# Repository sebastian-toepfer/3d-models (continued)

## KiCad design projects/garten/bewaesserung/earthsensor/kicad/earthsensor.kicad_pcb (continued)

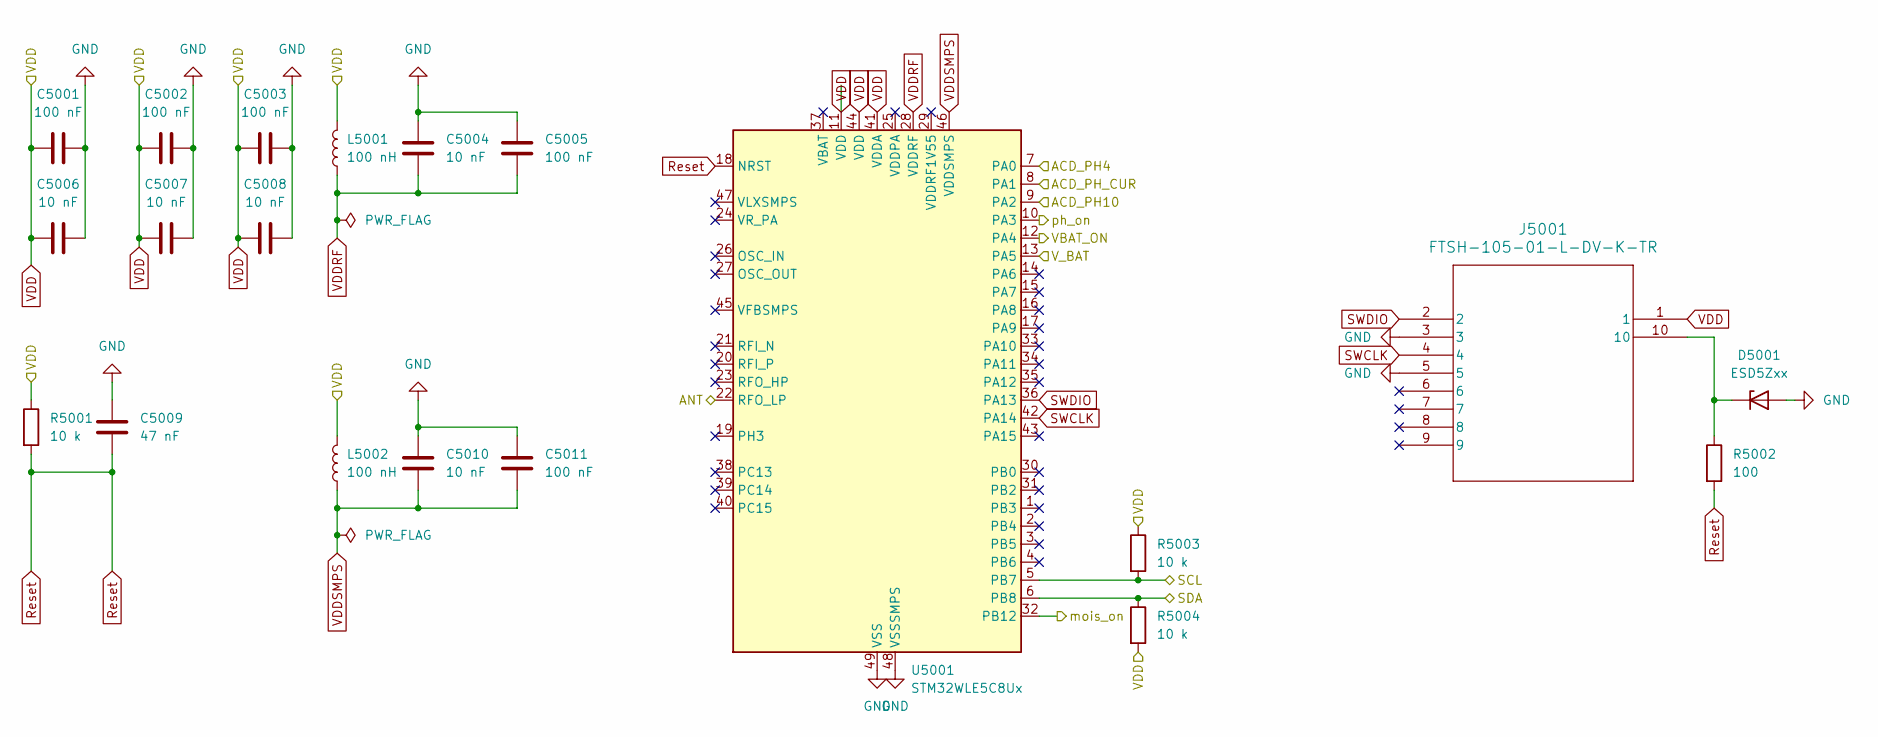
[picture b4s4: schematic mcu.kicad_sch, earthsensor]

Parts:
C5001, C5002, C5003, C5005, C5011: 100 nF; C_0805_2012Metric; MPN GCM21BR72A104KA37L
C5004, C5006, C5007, C5008, C5010: 10 nF; C_0805_2012Metric; MPN GRM2195C1H103FA01D
C5009: 47 nF; C_0805_2012Metric; MPN GCM21BR72A473KA37L
D5001: ESD5Zxx; D_SOD-523; MPN PESD5Z3.3-QX
J5001: FTSH-105-01-L-DV-K-TR; CON10_2X5_DUK_FTSH_SAI; MPN FTSH-105-01-L-DV-K-TR
L5001, L5002: 100 nH; L_0402_1005Metric; MPN LQW15ANR10J00D
R5001, R5003, R5004: 10 k; R_0402_1005Metric; MPN RN73H1ETTP1002B25
R5002: 100; R_0402_1005Metric; MPN RN73H1ETTP1000B25
U5001: STM32WLE5C8Ux; QFN-48-1EP_7x7mm_P0.5mm_EP5.6x5.6mm; MPN STM32WLE5C8U6

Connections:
/I2C.SCL: R5003.2, U5001.5 (PB7); also elsewhere on the board
/I2C.SDA: R5004.1, U5001.6 (PB8); also elsewhere on the board
/antenna/ANT: U5001.22 (RFO_LP); also elsewhere on the board
/mcu/ACD_PH4: U5001.7 (PA0); also elsewhere on the board
/mcu/ACD_PH10: U5001.9 (PA2); also elsewhere on the board
/mcu/ACD_PH_CUR: U5001.8 (PA1); also elsewhere on the board
/mcu/VBAT_ON: U5001.12 (PA4); also elsewhere on the board
/mcu/V_BAT: U5001.13 (PA5); also elsewhere on the board
/mcu/mois_on: U5001.32 (PB12); also elsewhere on the board
/mcu/ph_on: U5001.10 (PA3); also elsewhere on the board
GND: C5001.2, C5002.2, C5003.1, C5004.1, C5005.1, C5006.2, C5007.2, C5008.1, C5009.1, C5010.1, C5011.1, D5001.2 (A), J5001.3, J5001.5, U5001.48 (VSSSMPS), U5001.49 (VSS); also elsewhere on the board
unnamed: D5001.1 (K), J5001.10, R5002.1
Reset: C5009.2, R5001.2, R5002.2, U5001.18 (NRST)
SWCLK: J5001.4, U5001.42 (PA14)
SWDIO: J5001.2, U5001.36 (PA13)
VDD: C5001.1, C5002.1, C5003.2, C5006.1, C5007.1, C5008.2, J5001.1, L5001.2, L5002.2, R5001.1, R5003.1, R5004.2, U5001.11 (VDD), U5001.41 (VDDA), U5001.44 (VDD); also elsewhere on the board
VDDRF: C5004.2, C5005.2, L5001.1, U5001.28 (VDDRF)
VDDSMPS: C5010.2, C5011.2, L5002.1, U5001.46 (VDDSMPS)

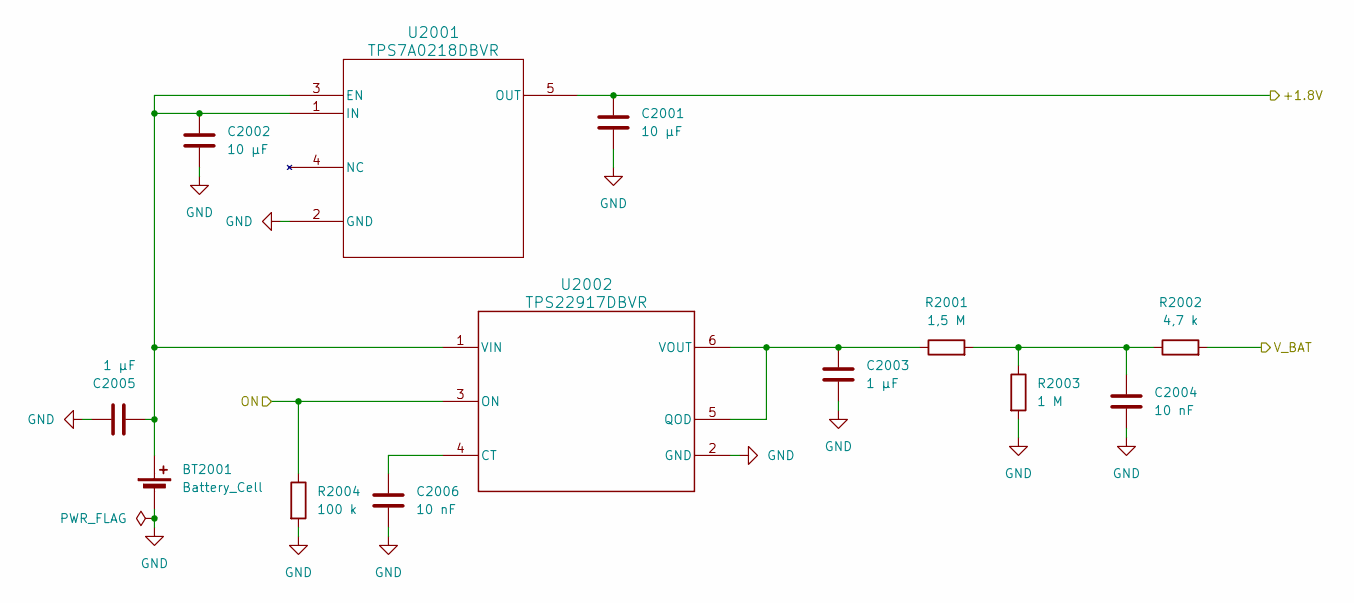
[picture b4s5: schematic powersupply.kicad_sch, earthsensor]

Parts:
BT2001: Battery_Cell; BAT_1016; MPN 1016
C2001, C2002: 10 µF; C_0805_2012Metric; MPN GRM21BR71A106KE51L
C2003, C2005: 1 µF; C_0805_2012Metric; MPN GCJ21BR71H105KA01L
C2004, C2006: 10 nF; C_0805_2012Metric; MPN GRM2195C1H103FA01D
R2001: 1,5 M; R_0402_1005Metric; MPN RK73H1ETTP1504F
R2002: 4,7 k; R_0402_1005Metric; MPN RN73R1ETTP4701B25
R2003: 1 M; R_0402_1005Metric; MPN RK73H1ETTP1004F
R2004: 100 k; R_0402_1005Metric; MPN RN73H1ETTP1003B25
U2001: TPS7A0218DBVR; SOT23_DBV_TEX-L; MPN TPS7A0218DBVR
U2002: TPS22917DBVR; DBV0006_N; MPN TPS22917DBVR

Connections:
/mcu/VBAT_ON: R2004.1, U2002.3 (ON); also elsewhere on the board
/mcu/V_BAT: R2002.2; also elsewhere on the board
GND: BT2001.2 (-), C2001.1, C2002.1, C2003.2, C2004.2, C2005.1, C2006.2, R2003.2, R2004.2, U2001.2 (GND), U2002.2 (GND); also elsewhere on the board
unnamed: BT2001.1 (+), C2002.2, C2005.2, U2001.1 (IN), U2001.3 (EN), U2002.1 (VIN)
unnamed: C2004.1, R2001.2, R2002.1, R2003.1
unnamed: C2006.1, U2002.4 (CT)
unnamed: C2003.1, R2001.1, U2002.5 (QOD), U2002.6 (VOUT)
VDD: C2001.2, U2001.5 (OUT); also elsewhere on the board

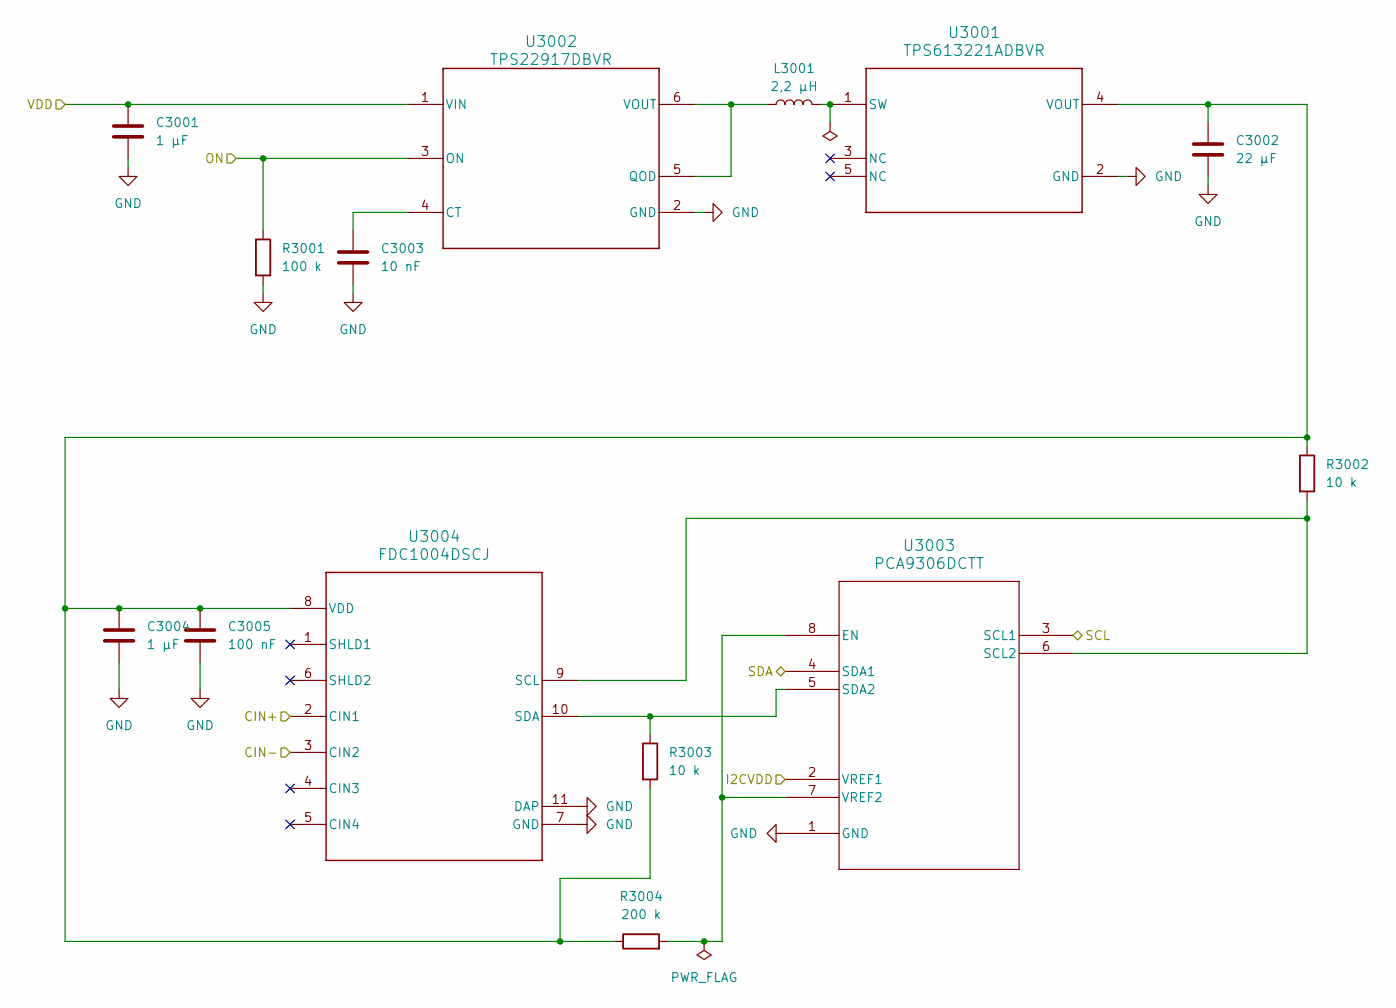
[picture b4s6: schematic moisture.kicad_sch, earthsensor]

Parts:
C3001, C3004: 1 µF; C_0805_2012Metric; MPN GCJ21BR71H105KA01L
C3002: 22 µF; C_1206_3216Metric; MPN GRM31CR71A226KE15K
C3003: 10 nF; C_0805_2012Metric; MPN GRM2195C1H103FA01D
C3005: 100 nF; C_0805_2012Metric; MPN GCM21BR72A104KA37L
L3001: 2,2 µH; L_0603_1608Metric; MPN LQM18PN2R2MGHD
R3001: 100 k; R_0402_1005Metric; MPN RN73H1ETTP1003B25
R3002, R3003: 10 k; R_0402_1005Metric; MPN RN73H1ETTP1002B25
R3004: 200 k; R_0402_1005Metric; MPN RN73H1ETTP2003B25
U3001: TPS613221ADBVR; DBV0005A_N; MPN TPS613221ADBVR
U3002: TPS22917DBVR; DBV0006_N; MPN TPS22917DBVR
U3003: PCA9306DCTT; DCT8; MPN PCA9306DCTT
U3004: FDC1004DSCJ; DSC0010B; MPN FDC1004DSCJ

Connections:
/I2C.SCL: U3003.4 (SDA1); also elsewhere on the board
/I2C.SDA: U3003.3 (SCL1); also elsewhere on the board
/mcu/mois_on: R3001.1, U3002.3 (ON); also elsewhere on the board
GND: C3001.2, C3002.2, C3003.2, C3004.2, C3005.2, R3001.2, U3001.2 (GND), U3002.2 (GND), U3003.1 (GND), U3004.7 (GND), U3004.11 (DAP); also elsewhere on the board
unnamed: L3001.2, U3001.1 (SW)
unnamed: C3002.1, C3004.1, C3005.1, R3002.1, R3003.2, R3004.1, U3001.4 (VOUT), U3004.8 (VDD)
unnamed: C3003.1, U3002.4 (CT)
unnamed: L3001.1, U3002.5 (QOD), U3002.6 (VOUT)
unnamed: R3004.2, U3003.7 (VREF2), U3003.8 (EN)
unnamed: R3002.2, U3003.6 (SCL2), U3004.9 (SCL)
unnamed: R3003.1, U3003.5 (SDA2), U3004.10 (SDA)
V2A_right: U3004.3 (CIN2); also elsewhere on the board
V2A_top: U3004.2 (CIN1); also elsewhere on the board
VDD: C3001.1, U3002.1 (VIN), U3003.2 (VREF1); also elsewhere on the board

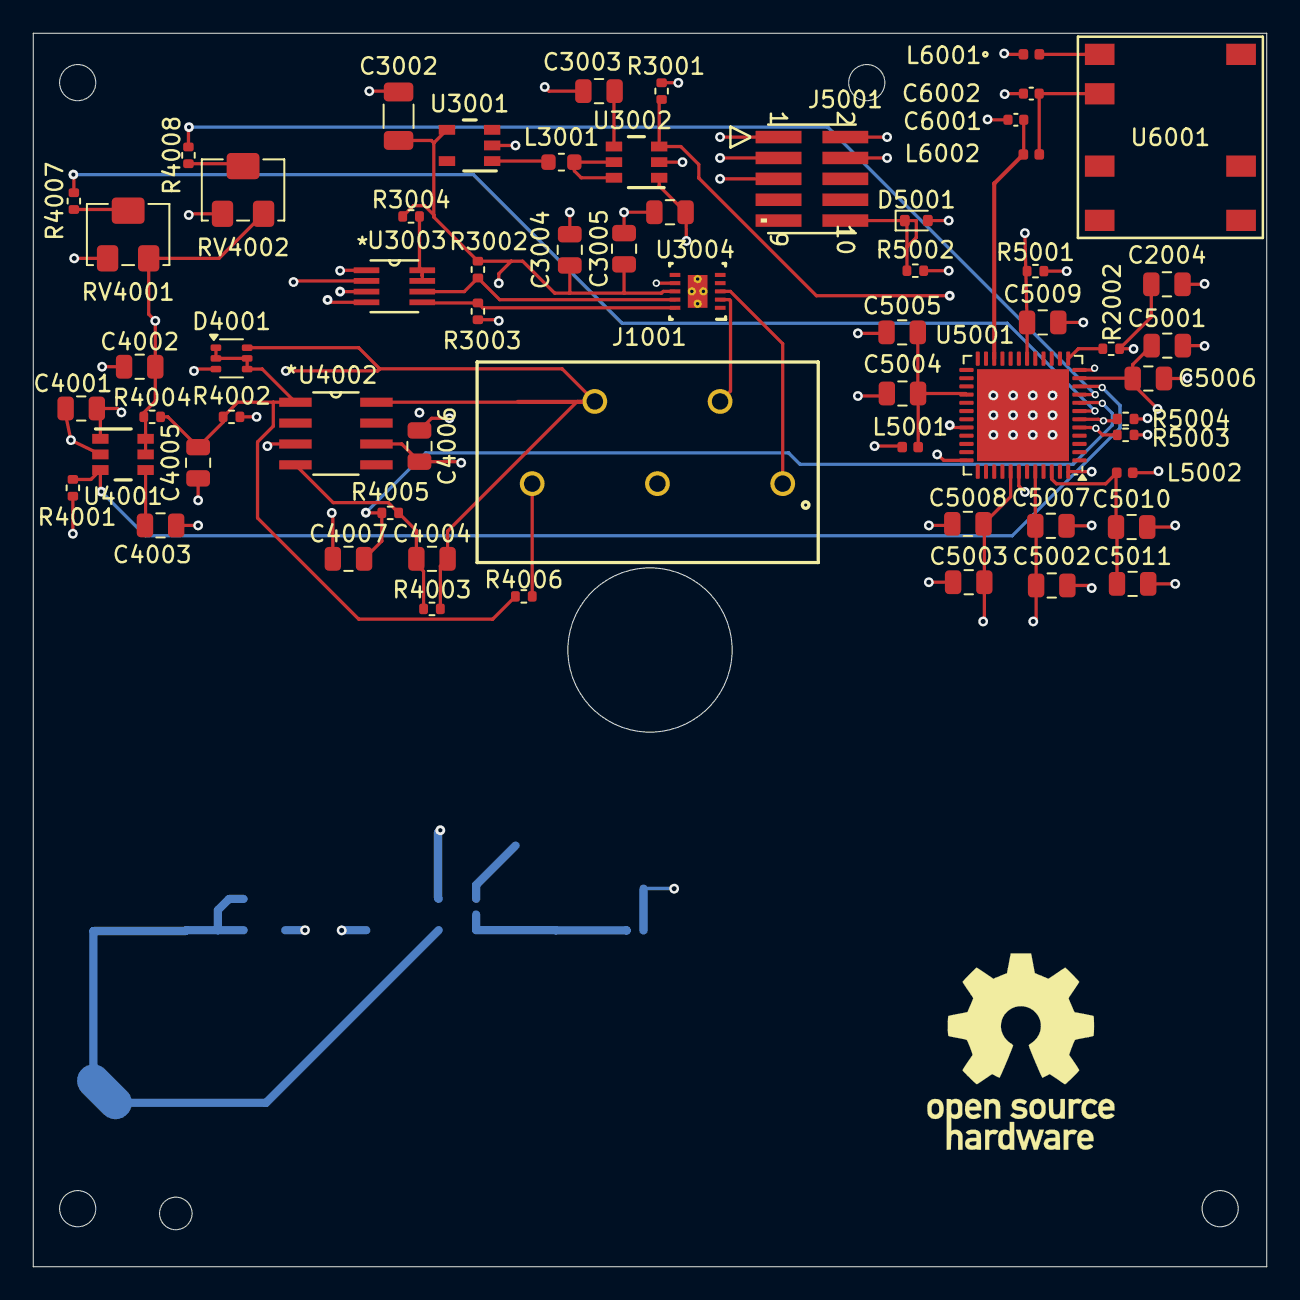
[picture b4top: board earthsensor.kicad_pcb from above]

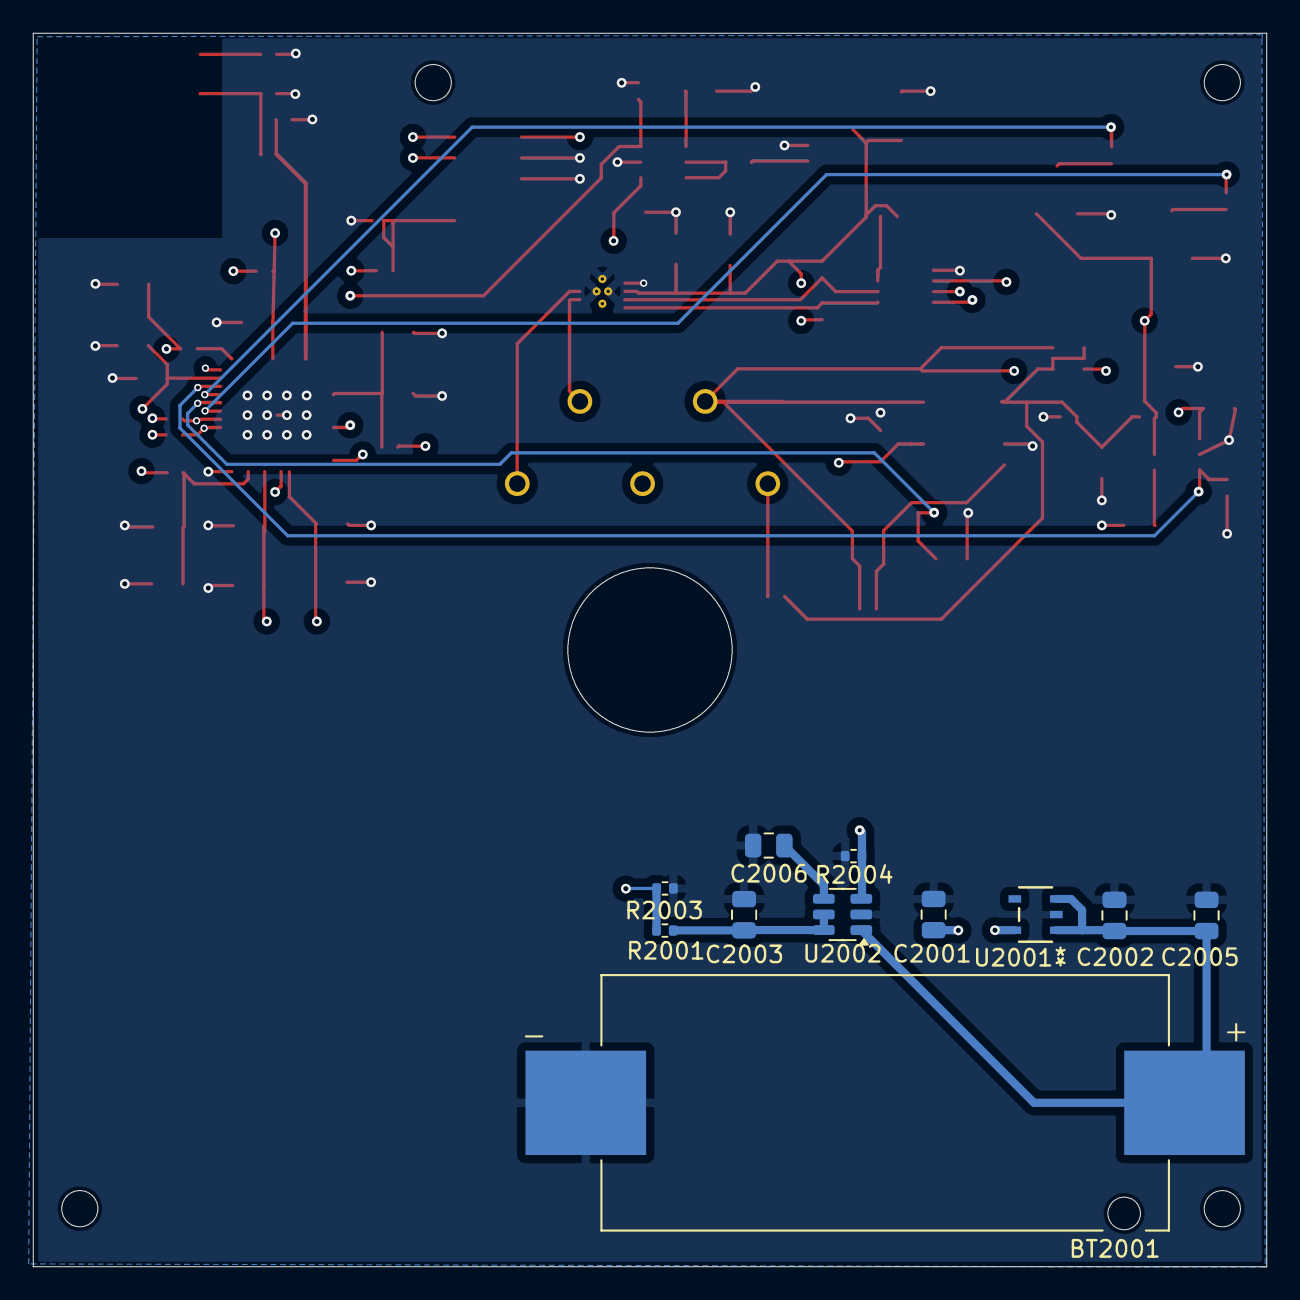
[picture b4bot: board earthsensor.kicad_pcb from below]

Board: 4 copper layers, 75.0 x 75.0 mm, 73 parts (11 on the bottom side), 41 nets.

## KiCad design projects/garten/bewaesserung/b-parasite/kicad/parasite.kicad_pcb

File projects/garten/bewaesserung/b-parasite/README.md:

This project is completly based on:

https://github.com/rbaron/b-parasite

⚠️  It has a difference License than the rest of my projects!

# License
The hardware and associated design files are released under the [Creative Commons CC BY-SA 4.0 license](https://creativecommons.org/licenses/by-sa/4.0/).
The code is released under the [MIT license](https://opensource.org/licenses/MIT).

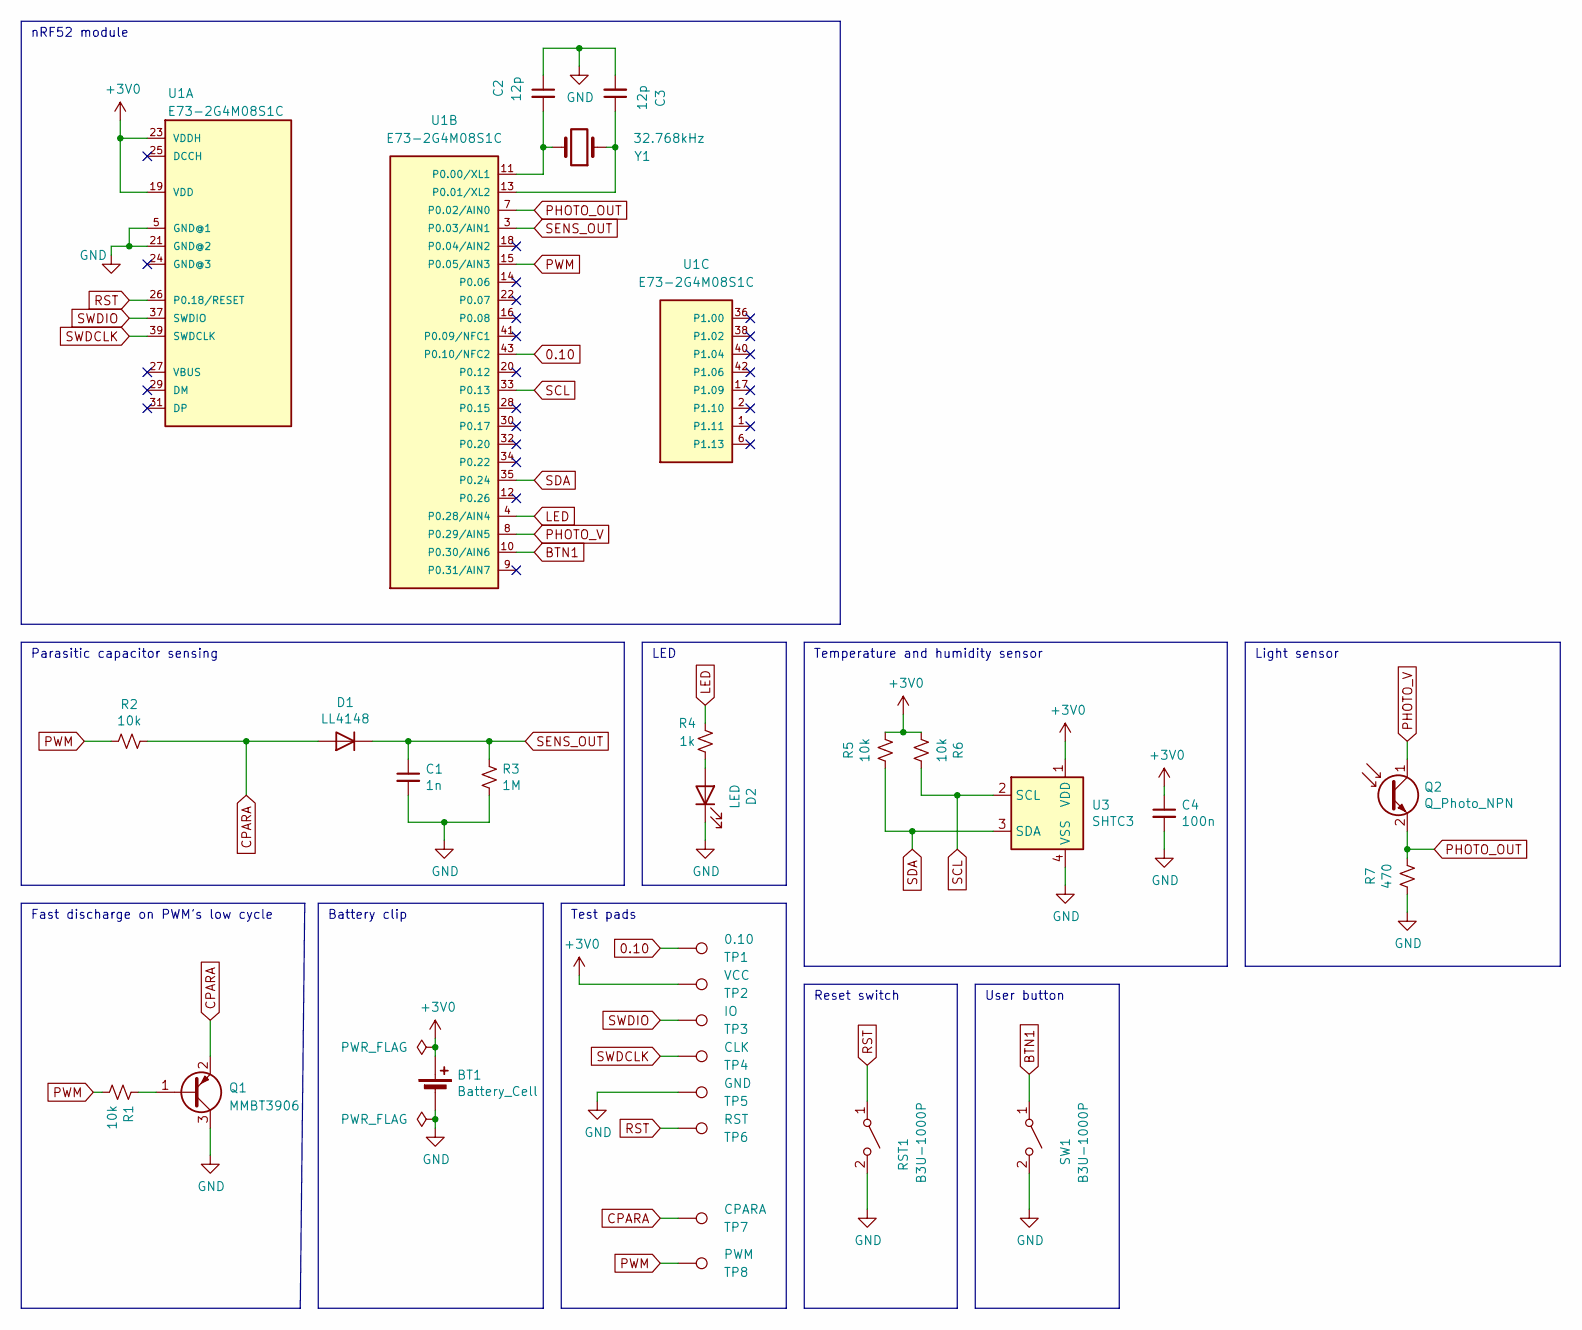
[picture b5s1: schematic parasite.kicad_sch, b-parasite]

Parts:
BT1: Battery_Cell; BatteryHolder_Keystone_3002_1x2032; MPN 3002TR
C1: 1n; C_0402_1005Metric; LCSC C1523
C2, C3: 12p; C_0402_1005Metric; MPN GRM1555C1H120GA01D; LCSC C1547
C4: 100n; C_0402_1005Metric; MPN GRM155R71A104KA01D; LCSC C1525
D1: LL4148; D_MiniMELF; MPN LL4148-GS18; LCSC C3011166
D2: LED; LED_0603_1608Metric; LCSC C2286
Q1: MMBT3906; SOT-23; MPN PZT3906; LCSC C2910191
Q2: Q_Photo_NPN; TR8; MPN ALS-PT19-315C/L177/TR8; LCSC C146233
R1, R2, R5, R6: 10k; R_0402_1005Metric; MPN CRGCQ0402F10K; LCSC C25744
R3: 1M; R_0402_1005Metric; MPN CRGCQ0402F1M0; LCSC C26083
R4: 1k; R_0402_1005Metric; MPN CRGCQ0402F1K0; LCSC C11702
R7: 470; R_0402_1005Metric; MPN RLP73N1ER47FTDF; LCSC C25117
RST1: B3U-1000P; SW_SPST_B3U-1000P; MPN B3U-1000P; LCSC C231329
SW1: B3U-1000P; SW_SPST_B3U-1000P; MPN B3U-1000P; LCSC C231329
TP1: 0.10; TestPoint_Pad_D1.0mm
TP2: VCC; TestPoint_Pad_D1.0mm
TP3: IO; TestPoint_Pad_D1.0mm
TP4: CLK; TestPoint_Pad_D1.0mm
TP5: GND; TestPoint_Pad_D1.0mm
TP6: RST; TestPoint_Pad_D1.0mm
TP7: CPARA; TestPoint_Pad_D1.0mm
TP8: PWM; TestPoint_Pad_D1.0mm
U1: E73-2G4M08S1C; MPN E73-2G4M08S1C
U3: SHTC3; Sensirion_DFN-4-1EP_2x2mm_P1mm_EP0.7x1.6mm; LCSC C194656
Y1: 32.768kHz; Crystal_SMD_3215-2Pin_3.2x1.5mm; MPN FC-135 32.7680KA-AC0; LCSC C32346

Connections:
0.10: TP1.1, U1.43 (P0.10/NFC2)
+3V0: BT1.1 (+), C4.1, R5.2, R6.1, TP2.1, U1.19 (VDD), U1.23 (VDDH), U3.1 (VDD)
BTN1: SW1.1 (A), U1.10 (P0.30/AIN6)
CPARA: D1.2 (A), Q1.2 (E), R2.2, TP7.1
GND: BT1.2 (-), C1.2, C2.1, C3.2, C4.2, D2.1 (K), Q1.3 (C), R3.2, R7.1, RST1.2 (B), SW1.2 (B), TP5.1, U1.5 (GND@1), U1.21 (GND@2), U3.4 (VSS)
LED: R4.2, U1.4 (P0.28/AIN4)
unnamed: D2.2 (A), R4.1
unnamed: Q1.1 (B), R1.1
unnamed: C2.2, U1.11 (P0.00/XL1), Y1.2
unnamed: C3.1, U1.13 (P0.01/XL2), Y1.1
PHOTO_OUT: Q2.2 (E), R7.2, U1.7 (P0.02/AIN0)
PHOTO_V: Q2.1 (C), U1.8 (P0.29/AIN5)
PWM: R1.2, R2.1, TP8.1, U1.15 (P0.05/AIN3)
RST: RST1.1 (A), TP6.1, U1.26 (P0.18/RESET)
SCL: R6.2, U1.33 (P0.13), U3.2 (SCL)
SDA: R5.1, U1.35 (P0.24), U3.3 (SDA)
SENS_OUT: C1.1, D1.1 (K), R3.1, U1.3 (P0.03/AIN1)
SWDCLK: TP4.1, U1.39 (SWDCLK)
SWDIO: TP3.1, U1.37 (SWDIO)

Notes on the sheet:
Fast discharge on PWM’s low cycle
Temperature and humidity sensor
LED
nRF52 module
Parasitic capacitor sensing
Test pads
Light sensor
Reset switch
User button
Battery clip

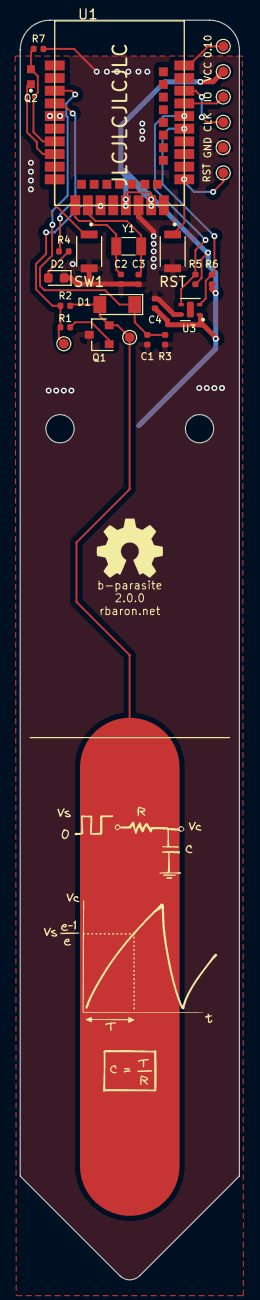
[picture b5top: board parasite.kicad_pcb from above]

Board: 2 copper layers, 22.0 x 126.4 mm, 29 parts (1 on the bottom side), 19 nets.

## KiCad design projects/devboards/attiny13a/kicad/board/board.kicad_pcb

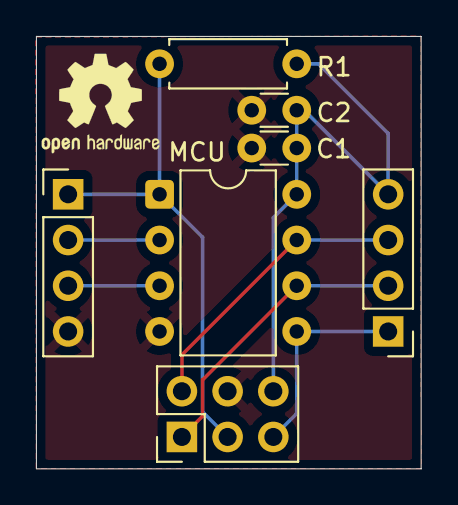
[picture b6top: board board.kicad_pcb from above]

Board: 2 copper layers, 21.4 x 24.0 mm, 7 parts (0 on the bottom side), 8 nets.

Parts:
C1: 10 nF; C_Disc_D3.0mm_W1.6mm_P2.50mm
C2: 100 nF; C_Disc_D3.0mm_W1.6mm_P2.50mm
J2: USBasp; PinHeader_2x03_P2.54mm_Vertical
J3: PinLeiste_Links; PinHeader_1x04_P2.54mm_Vertical
J4: PinLeiste_Rechts; PinHeader_1x04_P2.54mm_Vertical
MCU: Federkontakt; DIP-8_W7.62mm
R1: 10k; R_Axial_DIN0207_L6.3mm_D2.5mm_P7.62mm_Horizontal

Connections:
+5V: C1.1, C2.1, J2.6, J4.4, MCU.8, R1.1
COPI: J2.5, J4.1, MCU.5
GND: C1.2, C2.2, J2.4, J3.4, MCU.4
PB3: J3.2, MCU.2
PB4: J3.3, MCU.3
PICO: J2.1, J4.2, MCU.6
RESET: J2.3, J3.1, MCU.1, R1.2
SCK: J2.2, J4.3, MCU.7

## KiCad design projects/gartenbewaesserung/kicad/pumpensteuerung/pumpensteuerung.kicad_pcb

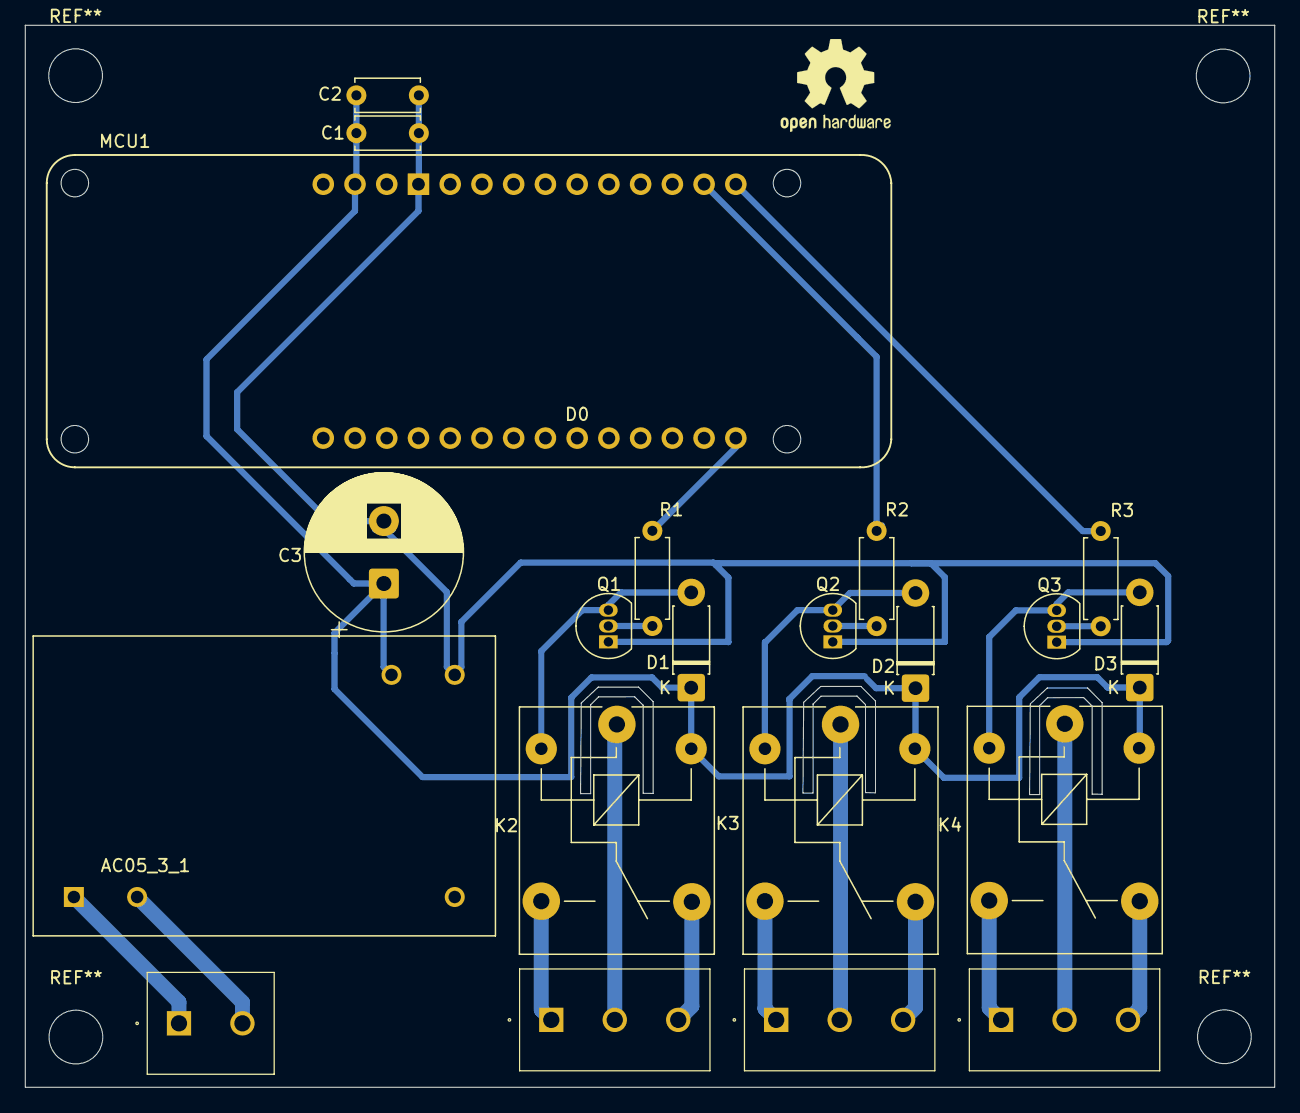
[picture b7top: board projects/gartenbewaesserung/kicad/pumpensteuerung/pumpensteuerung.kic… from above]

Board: 2 copper layers, 100.0 x 85.0 mm, 21 parts (0 on the bottom side), 22 nets.

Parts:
AC05_3_1: AZ_PSU_Module
C1: 10000pF 100V 10% Y5P 5mm; C_Disc_D5.0mm_W2.5mm_P5.00mm
C2: 0.1uF 500V +80/-20%; C_Disc_D5.0mm_W2.5mm_P5.00mm
C3: 1000 µF, 25 V, 105°C, low ESR, 12,5 x 20 mm, RM 5; CP_Radial_D12.5mm_P5.00mm
D1, D2, D3: 1N4007; D_DO-41_SOD81_P7.62mm_Horizontal
J1, J4, J5: Screw_Terminal_01x03; MKDSN 1,5_3-5,08
J2: Screw_Terminal_01x02; MKDSN 1,5_2-5,08
K2, K3, K4: SANYOU_SRD_Form_C; Relay_SPDT_SANYOU_SRD_Series_Form_C
MCU1: Arduino_MKR_WAN_1310_Socket; Arduino_MKR_FOX_1200_Socket
Q1, Q2, Q3: 2N3904; TO-92_Inline
R1, R2, R3: 220 Ohm, axial, 250 mW, 0,1%; R_Axial_DIN0207_L6.3mm_D2.5mm_P7.62mm_Horizontal

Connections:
/+5V: AC05_3_1.3 (+V), C1.1, C2.1, C3.1, D1.1 (K), D2.1 (K), D3.1 (K), K2.5, K3.5, K4.5, MCU1.VIN
/-5V: AC05_3_1.4 (-V), C1.2, C2.2, C3.2, MCU1.GND, Q1.1 (E), Q2.1 (E), Q3.1 (E)
/Bewaesserungsrelais: MCU1.D7, R2.1
/Bewaesserungsrelais/IN: J4.2, K3.1
/Bewaesserungsrelais/NO: J4.3, K3.4
/Bewaesserungsrelais/ON: J4.1, K3.3
/Hauptrelais: MCU1.D5, R1.1
/Hauptrelais/IN: J1.2, K2.1
/Hauptrelais/NO: J1.3, K2.4
/Hauptrelais/ON: J1.1, K2.3
/Poolrelais: MCU1.D6, R3.1
/Poolrelais/IN: J5.2, K4.1
/Poolrelais/NO: J5.3, K4.4
/Poolrelais/ON: J5.1, K4.3
GND: AC05_3_1.2 (AC/N), J2.2
unnamed: D1.2 (A), K2.2, Q1.3 (C)
unnamed: D2.2 (A), K3.2, Q2.3 (C)
unnamed: D3.2 (A), K4.2, Q3.3 (C)
unnamed: Q1.2 (B), R1.2
unnamed: Q2.2 (B), R2.2
unnamed: Q3.2 (B), R3.2
VCC: AC05_3_1.1 (AC/L), J2.1

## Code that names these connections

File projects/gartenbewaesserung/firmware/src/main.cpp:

#include "pinmap.h"
#include <Arduino.h>

// cppcheck-suppress unusedFunction
void setup()
{
  pinMode(PIN_HAUPTRELAIS, OUTPUT);
  pinMode(PIN_POOLRELAIS, OUTPUT);
  pinMode(PIN_BEWAESSERUNGSRELAIS, OUTPUT);
}

// cppcheck-suppress unusedFunction
void loop()
{
}

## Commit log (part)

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2023-09-09 add add hose table clamp
2023-09-09 simplify calculations
2023-09-09 rounding some edges
2023-09-12 extend generation of stl with parameter support
2023-09-12 update action to commit updated generated models
2023-09-12 move mirror_copy into lib
2023-09-12 fix issue in gh actions
2023-09-12 update generated models
2023-09-12 use another action to push back the changed code
2023-09-12 enable manual workflow trigger
2023-09-12 remove generated from gitignore
2023-09-12 add installation of stl-tumb to gh action
2023-09-12 add generation of previews to gh action
2023-09-14 fix gh action -> apt-get update is your friend
2023-09-14 add parameter file for magnetic hose connector
2023-09-14 add a magnetic hose connector
2023-09-14 add vi swap files to gitignore
2023-09-14 add lib to support polar pattern ala freecad
2023-09-15 add module with adapter for tilt window exhaust hood
    more or less an openscad version of the upper part of part 1 of
    https://www.thingiverse.com/thing:4148187
2023-09-16 finishes tutorial ch01
2023-09-16 finishes tutorial ch03
2023-09-16 finishes tutorial ch04
2023-09-16 finishes tutorial ch07
2023-09-16 finishes tutorial ch05
2023-10-03 finishes tutorial ch08
2023-10-03 tutorial ch09
    not complete ... a lot of c&p to define a pologon and so one ... stopping
    here!
2023-12-15 Bump actions/upload-artifact from 3 to 4
    Bumps [actions/upload-artifact](https://github.com/actions/upload-artifact) from 3 to 4.
    - [Release notes](https://github.com/actions/upload-artifact/releases)
    - [Commits](https://github.com/actions/upload-artifact/compare/v3...v4)
    ---
    updated-dependencies:
    - dependency-name: actions/upload-artifact
2024-03-31 add lib to create arc's
2024-03-31 add teufel speaker center cs35 c mk3
2024-03-31 add teufel speaker satellite cs25 fcr mk3
2024-03-31 rename polar function to match my new naming rules
2024-03-31 rename sector_arc function to match my new naming rules
2024-04-01 macht die teufel etwas groesser
2024-04-01 fuegt erst version eines center speaker holders hinzu
2024-04-08 rename inc back to scad
2024-04-13 format everything
2024-04-20 copy new generated stls into a seperate folder
2024-04-20 fix typo in eckwinkel
2024-05-06 search desings in depper folder structure
2024-05-06 fix generator script to use libs under libs
2024-05-06 add threadlib
2024-05-06 fuegt einfach box mit befestigung an aluprofil hinzu
2024-05-06 fuegt deckel fuer einfach box hinzu
2024-05-26 ersetzt befestigungsloch in schlauchbefestigung mit "teil"
2024-05-26 fuegt bein des monitorstands von playseat hinzu
2024-05-26 fuegt teil fuer schraubbfestigungen hinzu
2024-05-26 fuegt befestigung fuer den satelliten lautsprecher hinzu
2024-05-26 fuegt eine fake nut hinzu
2024-05-26 verschiebt center speaker in neuen unterordner
2024-05-30 add ground spike for small solar light
2024-06-17 verkleinert mitleren steg in holder fuer statelite
2024-07-20 split satelliten holder in modules
2024-07-27 fix typo in makefile
2024-07-27 replace generate of non param desgins with makefile generation
2024-07-28 use shell script as adapter-pattern to make
2024-07-28 replace shellscript with make in ghaction
2024-08-05 definiert ein paar functionen um groessen zu ermitteln
2024-08-05 stellt center ls halter auf function um
2024-08-06 fuegt besser befestigung fuer satellite speaker hinzu
2024-08-10 Create LICENSE
2024-08-12 add 3mf to makefile
2024-08-12 remove tutorial files from desgins
2024-08-14 fuegt einfache roehre als lib hinzu
2024-08-31 add restore-mtime so that make works better in gh actions
2024-08-31 add action to automatic rebase pull requests
2024-08-31 fix c&p issue
2024-08-31 recreate satelite halter with modules
2024-08-31 recreate satelliten halter
2024-09-02 fuegt eine magnethalter fuer trinkschlauch hinzu
2024-09-09 replace auto union with expliced
2024-10-20 add simucube 2 pro psu placeholder thing
2024-10-20 add simucube 2 pro psu winkel holder
2024-10-20 add simucube 2 pro psu eck holder
2024-10-29 fuegt abstandshalter fuer quickrelase hinzu
2024-11-11 fuegt klappenbefestigung fuer alten loewe roehren tv hinzu
2025-06-03 [gartenbewaesserung] exclude kicad backup folder
2025-06-03 [gartenbewaesserung(pcb)] stellt export des pcb auf stl mit manuell gesetzten grid origin um
    das manuelle setzen ist leider notwendig, damit wir das board einfacher
    in openscad importieren koennen. sonst verwendet kicad das 'blatt' und
    somit muessen wir rechnen wo das board liegt. um es dann in openscad zu
    zentrieren. sicher koennte man das im makefile machen und da dann auch
    gleich die transfromation mit generieren. nur das steht gerade in keinem
    verhaeltnis.
2025-06-03 [gartenbewaesserung(model)] fuegt nasen an das gehaeuseunterteil fuer die verbindung mit dem oberteil
2025-06-03 [gartenbewaesserung(model)] fuegt gehaeuse oberseite hinzu
2025-06-03 [gartenbewaesserung(build)] extend makefile to generate as much as posible
    - create step from current pcb
    - convert step to stl to be usable inside openscad
    - to be printable
    - create stl from all openscad parts
    - create 3mf from all openscad parts
2025-06-03 [gartenbewaesserung(pcb)] fix some issue in pcb
2025-06-03 [gartenbewaesserung(model)] add pcb to model
2025-06-03 [gartenbewaesserung(pcb)] try to improve kicad project specific libs
2025-06-03 [gartenbewaesserung(pcb)] increase gap between high and low voltage
2025-06-03 [gartenbewaesserung(model)] fuegt oeffnungen fuer die schraubterminals hinzu
2025-06-03 [gartenbewaesserung(model)] fix gehaeuse parts to match pcb :)
2025-06-03 [gartenbewaesserung(firmware)] start with firmware
2025-06-03 [gartenbewaesserung(model)] improve gehaeuse model
2025-06-03 [gartenbewaesserung(pcb)] 'airgap' between high voltage and low voltage
2025-06-03 [gartenbewaesserung(model)] fix gehaeuse unterseite to match pcb :)
2025-06-08 [gartenbewaesserung(firmware)] remove linter
2025-06-08 [gartenbewaesserung(firmware)] add pump with two valves
2025-06-10 [gartenbewaesserung(firmware)] use dispatcher to switch valves
    allow to use different lora ports to change state of a valve.
    currently it only support on/off per port/group!
2025-06-10 [gartenbewaesserung(firmware)] add a daily beacon to show gateways we're still alive
    RTC Implementation is mostly a copy of code from chatgpt.
2025-06-20 [gartenbewaesserung(model)] add hole for sma connector
2025-06-22 fix generation of stl and 3mf
2025-06-28 [gartenbewaesserung(pcb)] move power supply a litle bit
    move the power supply a little bit more into the center, so we have more
    clearance in the case.
2025-06-28 [gartenbewaesserung(model)] add screw holes to fix pcb
2025-06-28 [gartenbewaesserung(pcb)] change resistor to 220 Ohm
    1k was a little bit too much, for 3.3V.
2025-06-28 [gartenbewasserung(pcb)] replace Q8050 with a 2N3904
2025-06-28 [gartenbewaesserung(pcb)] add MPN to easier pcb ordering
2025-06-28 [gartenbewaesserung(pcb/firmware)] generate pinmap from schematic
2025-06-28 [gartenbewaesserung(pcb)] add oshw logo
2025-07-05 convert ersatzteile to a project
2025-07-05 convert abluft snapy to a project
2025-07-05 convert solar erdspies to a project
2025-07-05 convert psu holder to project
2025-07-05 makes gartenbewasserung part of my garten projects
2025-07-05 convert speaker holder to projects
2025-07-05 convert racing_rig storage_box to project
2025-07-05 add makefile to make everything
2025-07-05 move tools into shared
2025-07-05 add readme to explain my structur
2025-07-05 fix readme format -> writing a markdown without markdown :)
2025-07-06 Fix minor bugs in firmware
2025-07-06 remove redundandency from makefiles
2025-07-06 fix typo in digital_output_pin for ardunino
2025-07-06 [garten/bewaesserung(firmware)] fix pump error handling
2025-07-08 Update LICENSE
2025-07-08 Create LICENSE.cern-ohl-w
2025-07-09 Add license headers
2025-07-09 Add license headers to sourcecode
2025-07-11 rename bewaesserung to pumpensteuerung and make it a subproject of bewaesserung
2025-07-14 [garten/bewaesserung/b-parasite(pcb)] fix all ERC violations
2025-07-24 extends openscad with lib path and to be usable on macos and linux
2025-07-27 [pool/pool(model)] add thread to skimmer cover
    should allow to attach the electronic to it.
2025-08-03 [earthsensor(model)] add bottom with earthspike holder threads
2025-08-03 add pg threads lookup table
2025-08-03 add a spike as shared part
2025-08-03 [earthsnsor(model}] add spike holder
2025-08-03 add metadata to playset tripel tv stand
2025-08-03 add metadata to simucube 2 pro
2025-10-11 [earthsnsor(model)] add spike holder
2025-10-11 [earthsensor(pcb)] add pcb desgined with the help of chatgpt
    most decisions were made using chatgpt
2026-02-25 [garten/bewaesserung] change powersupply from 230VAC to 24VDC
2026-03-26 WIP: add Phil's Lab TI-MSPM0 Tutorial Board
2026-04-10 [garten/bewaesserung] add new hole into housing for new relay
2026-04-10 [garten/bewaesserung(pcb)] move relays a littlebit more into center
2026-04-10 [garten/bewaesserung(pcb)] rotate powersupply connector
2026-04-10 [garten/bewaesserung(circuit) add circuitdiagram
2026-04-10 [garten/bewaesserung(model)] fix relay and sma holes
2026-05-05 [garten/bewaesserung(firmware)] add posibility to lock a valve
2026-05-05 [garten/bewaesserung(firmware)] add lora handling to lock a valve
2026-05-11 [garten/bewaesserung(model)] move sma hole to have more space for the arduino
2026-05-11 [garten/bewasserung(firmware)] update toolchan-gccarmnoneeabi to 1.140201.0
2026-05-29 [garten/bewaesserung(firmware) move pump into lib
2026-05-29 [garten/bewaesserung(firmware)] add tests
2026-05-29 [garten/bewaesserung(firmware)] split gpio lib into api and impl.
2026-05-29 [garten/bewaessertung(firmware)] extract valves from pump
2026-05-29 [garten/bewaesserung(firmware)] format also h files
2026-06-01 [garten/bewasserung(firmware)] add warning if not all pins are define in pinmap.h
2026-06-04 [garten/bewaesserung(firmware)] move pump into lib
2026-06-06 [garten/bewaesserung(firmware)] introduce usecases
2026-06-06 [garten/bewaesserung(firmware)] clean up gpio lib
    - move headers into subfolders (gpio, gpio/<platform>)
    - rename pin.h to pin_config.h
    - rename digital_pin_info_t to pin_config
    - rename platform_info property to platform_config
    - remove gpio_arduino -> not used anymore
2026-06-06 [garten/bewaesserung(firmware)] intoduce a small memory abstraction layer
2026-06-15 [garten/bewaesserung(firmware)] configure library source discovery via library.json
    - set includeDir/srcDir in library.json so PlatformIO finds headers in src/
    - fix memory header path from memory/mem.h.h to mem/mem.h
    - remove unused symlink deps for headerless impl libs
    - keep explicit_library_sources.py and custom_explicit_library_sources for headerless libraries
2026-06-17 [garten/bewaesserung] rename to garten/bewaesserung/lopump
